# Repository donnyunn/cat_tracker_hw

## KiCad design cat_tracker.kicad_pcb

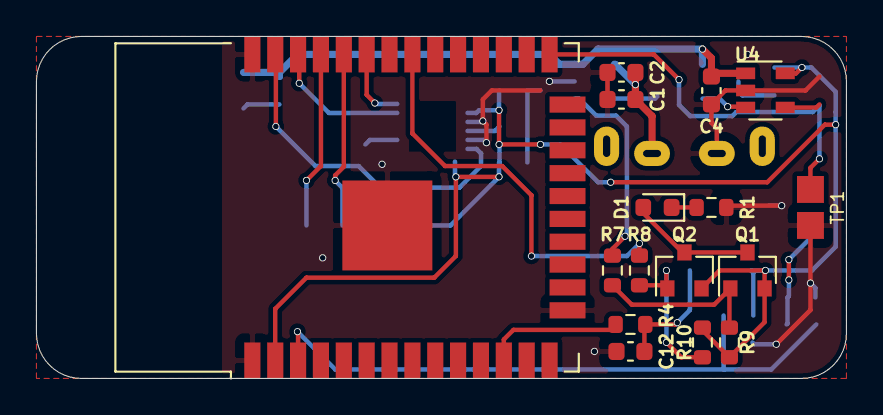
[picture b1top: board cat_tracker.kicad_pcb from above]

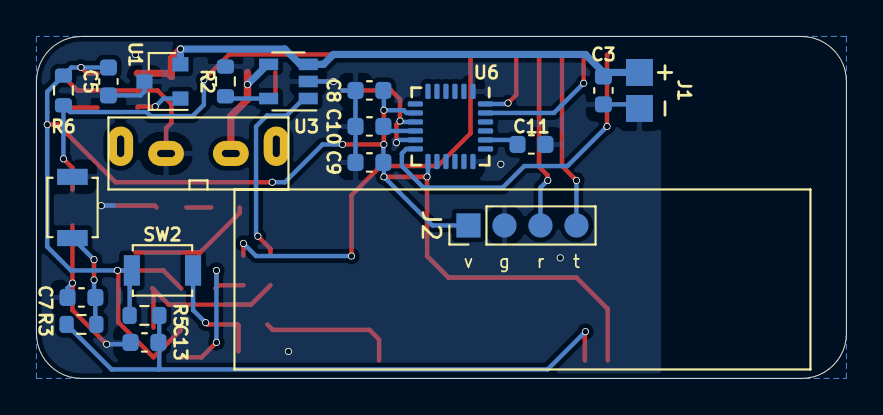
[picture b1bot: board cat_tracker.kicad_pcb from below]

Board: 2 copper layers, 45.0 x 19.0 mm, 36 parts (20 on the bottom side), 24 nets.

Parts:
C1, C3: 10u; C_0603_1608Metric
C2, C4, C5, C7, C9, C10, C12: 100n; C_0603_1608Metric
C8: 10n; C_0603_1608Metric
C11: 2.2n; C_0603_1608Metric
C13: 1u; C_0603_1608Metric
D1: LED/1608; LED_0603_1608Metric
J1: Conn_01x02; boot
J2: ISP; PinHeader_1x04_P2.00mm_Vertical
Q1, Q2: pnp; SOT-23
R1: 510; R_0603_1608Metric
R2: 2k; R_0603_1608Metric
R3: 0; R_0603_1608Metric
R4: 1k; R_0603_1608Metric
R5, R6: 10k; R_0603_1608Metric
R7, R8, R9, R10: 33k; R_0603_1608Metric
SW1: EN Btn; SW_SPST_B3U-1000P
SW2: Btn; SW_SPST_B3U-1000P
TP1: boot
U1: MCP100-315D; SOT-23
U2: USB_CType_2Pin
U3: MCP73831; SOT-23-5
U4: MIC5318-3.3YD5-TR; SOT-23-5
U5: ESP32-WROOM-32E; ESP32-WROOM-32
U6: MPU-6050; InvenSense_QFN-24_4x4mm_P0.5mm

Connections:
+3V3: C5.1, C8.1, C9.1, J2.1, Q1.2, Q2.2, R5.2, R6.2, R9.1, R10.1, SW2.1, U4.5, U5.2, U6.8, U6.13
BATT: C3.1, C4.1, J1.1, U1.2, U3.3, U4.1
BOOT: R6.1, TP1.2, U5.25
BTN: R4.1, U5.12
CHRG: R7.2, U3.1
EN: C13.1, R3.1, R5.1, U5.3
Earth: C1.2, C2.2, C3.2, C4.2, C5.2, C7.2, C8.2, C9.2, C10.1, C11.1, C12.2, C13.2, J1.2, J2.2, R1.2, R2.2, SW1.1, TP1.1, U1.3, U2.12, U3.2, U4.2, U5.1, U5.15, U5.38, U5.39, U6.1, U6.9, U6.11, U6.18
INT: U5.37, U6.12
LED: R8.2, U5.31
unnamed: C7.1, R3.2, SW1.2
unnamed: C10.2, U6.10
unnamed: C11.2, U6.20
unnamed: C12.1, R4.2, SW2.2
unnamed: D1.1, R1.1
unnamed: D1.2, Q1.3, Q2.3
unnamed: Q1.1, R7.1, R9.2
unnamed: Q2.1, R8.1, R10.2
unnamed: R2.1, U3.5
unnamed: U1.1, U4.3
RX: J2.3, U5.34
SCL: U5.36, U6.23
SDA: U5.33, U6.24
TX: J2.4, U5.35
VBUS: C1.1, C2.1, U2.9, U3.4

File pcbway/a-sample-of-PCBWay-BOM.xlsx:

|  |  | xxxx xxxx xxxxx xxPCS BOM (Sample Bill of Materials)
Item # | *Designator | *Qty | Manufacturer | *Mfg Part # | Description / Value | *Package/Footprint | Type | Your Instructions / Notes
1 | C1,C3 | 2 |  |  | 10uF | 0603 | SMD
2 | C11 | 1 |  |  | 2.2nF | 0603 | SMD
3 | C13 | 1 |  |  | 1uF | 0603 | SMD
4 | C2,C4,C5,C7,C9,C10,C12 | 7 |  |  | 100nF | 0603 | SMD
5 | C6,C8 | 2 |  |  | 10nF | 0603 | SMD
6 | D1 | 1 | Kingbright | AP1608SRCPRV | Standard LEDs - SMD RED WATER CLEAR | 0603 | SMD
7 | Q1,Q2 | 2 | Nexperia | BC856B,215 | Bipolar Transistors - BJT PNP GP 100MA 65V | SOT-23 | SMD
8 | R1 | 1 |  |  | 510Ω | 0603 | SMD
9 | R2 | 1 |  |  | 2kΩ | 0603 | SMD
10 | R3 | 1 |  |  | 0Ω | 0603 | SMD
11 | R4 | 1 |  |  | 1kΩ | 0603 | SMD
12 | R5,R6 | 2 |  |  | 10kΩ | 0603 | SMD
13 | R7,R8 | 2 |  |  | 33kΩ | 0603 | SMD
14 | SW2 | 1 | Omron Electronics | B3U-1000P | Tactile Switches Top Actuated w/o boss w/o ground |  | SMD
15 | U1 | 1 | Microchip Technology | MCP100T-315DI/TO | Supervisory Circuits | SOT-23 | SMD
16 | U3 | 1 | Microchip Technology | MCP73831T-2ACI/OT | Battery Management Charge mgnt contr | SOT-23-5 | SMD
17 | U4 | 1 | Microchip Technology | MIC5318-3.3YD5-TR | LDO Voltage Regulators 6Vin, Single 300mA ULDO | SOT-23-5 | SMD
18 | U5 | 1 | Espressif Systems | ESP32-WROOM-32E(M113EH2800PH3Q0) | WiFi Modules - 802.11 SMD Module ESP32-WROOM-32E, ESP32-D0WD-V3, 16 MB SPI flas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 |  | SMD
19 | U6 | 1 | TDK InvenSense | MPU-6050 | IMUs - Inertial Measurement Units 6-Axis MEMS MotionTracking Device with DMP | QFN-24 | SMD
Need a quick and accurante quote? Need an efficient production? Please read SMT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
Click for Instructions on How to Create a BOM

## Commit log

2021-08-09 2021-08-09
2021-08-09 2021-08-09 2
2021-08-10 2021-08-10
2021-08-10 2021-08-10 2
2021-08-29 2021-08-29
2021-08-30 2021-08-30
2021-09-08 2021-09-08
2021-09-17 2021-09-17
2021-12-14 2021-12-14
